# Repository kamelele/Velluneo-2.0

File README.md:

# Velluneo-2.0

[Projekt E27 z wymiennym wkładem LED](hardware/E27/README.md)

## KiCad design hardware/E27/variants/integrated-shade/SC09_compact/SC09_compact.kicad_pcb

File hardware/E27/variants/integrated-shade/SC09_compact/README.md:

Current desk-reviewed laboratory candidate: [SB01-R2](README.SB01-R2.md). Earlier R1 release files and descriptions below are historical.

Historical R1 engineering candidate: [SC09-SB01 simplified procurement](README.SB01.md). The following older text and release-candidate artifacts are historical.

# SC09-ROUTE05 bare-PCB/manual prototype candidate

Current packet: workflow/integrated-shade/compact-09/routing-order-prep/po_poprawkach. PCB51.2x33mm,2layers,1.6mm FR4,1oz,lead-freeHASL; unchangedCAT01 electronics and component placements. The outline adds edge margin, D1 return via is outside its SMD solder land and the bottom AC legend is clear of solder apertures. AC RIGHT/LED LEFT in common topCAD coordinates. Physical vent-face clearance remains5mm. Current exact fabrication release decision remains pending; full-product qualification is not asserted. No order or powered test.

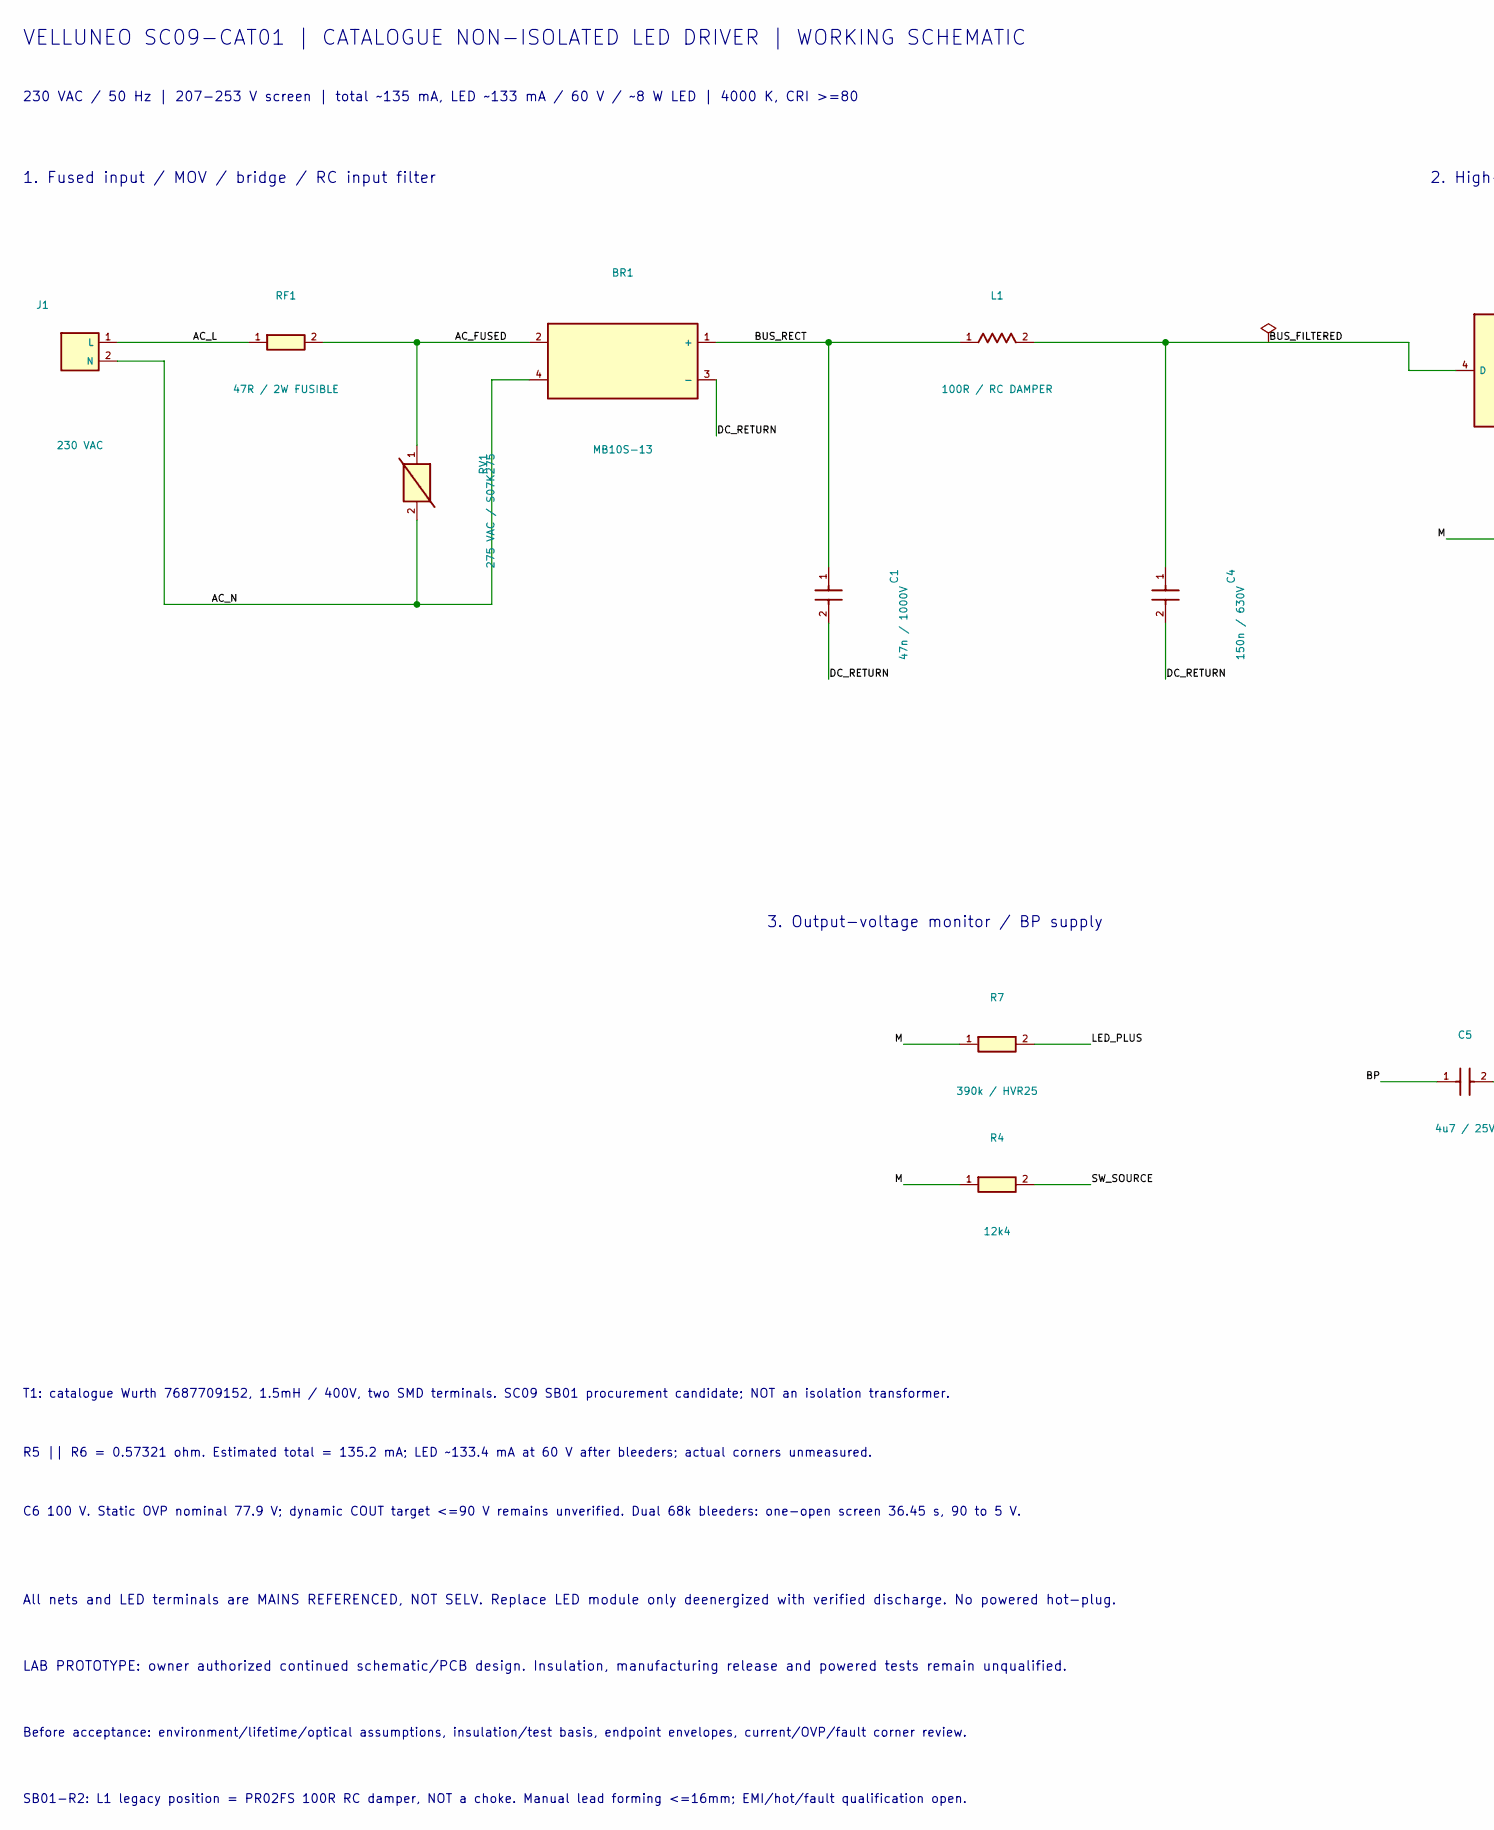
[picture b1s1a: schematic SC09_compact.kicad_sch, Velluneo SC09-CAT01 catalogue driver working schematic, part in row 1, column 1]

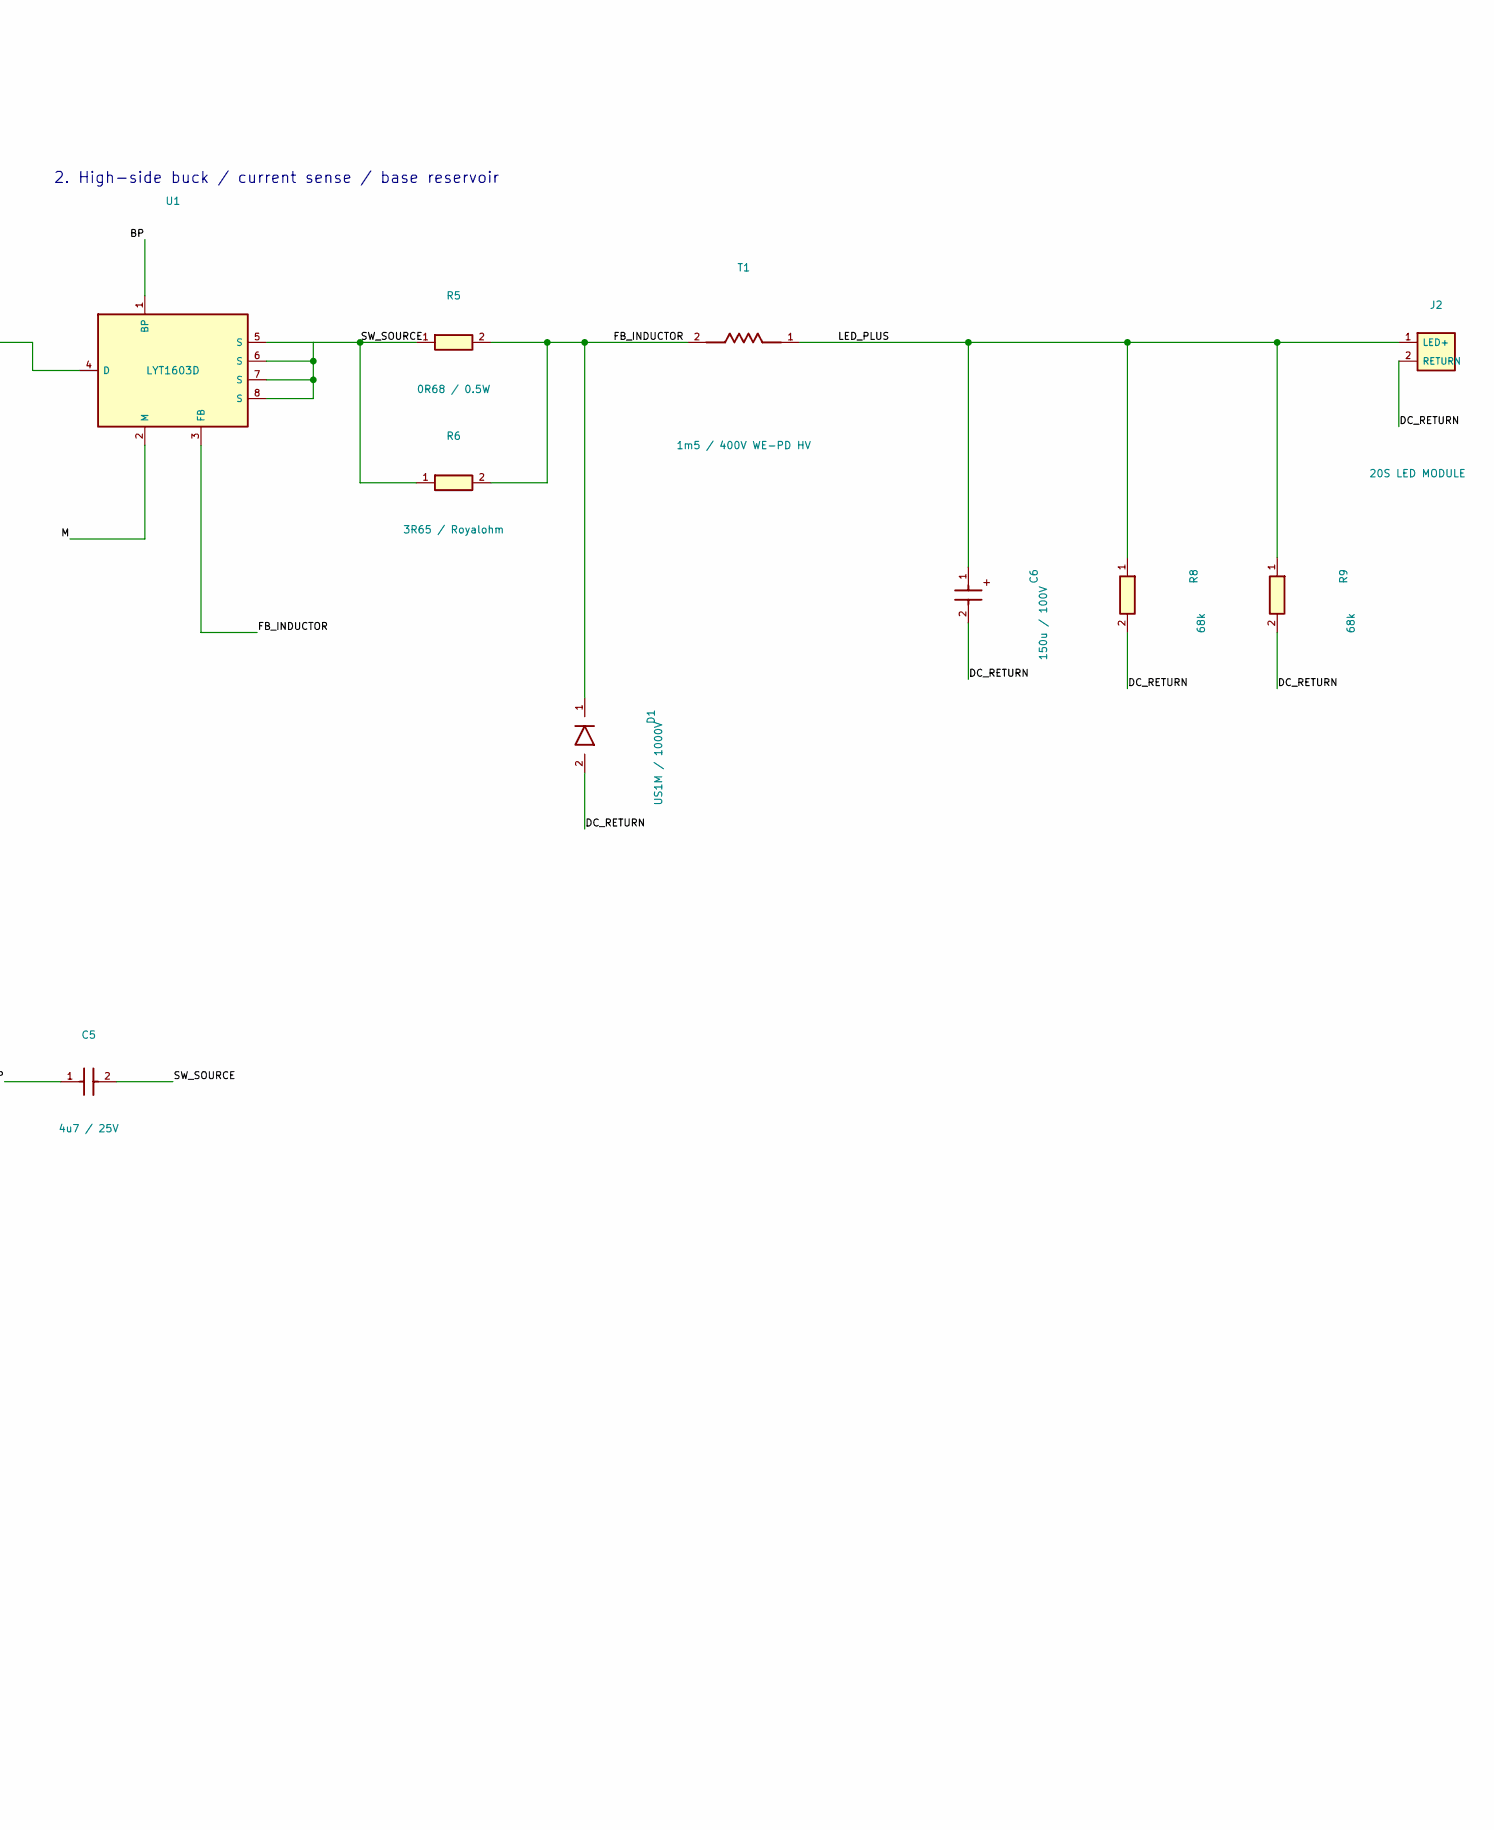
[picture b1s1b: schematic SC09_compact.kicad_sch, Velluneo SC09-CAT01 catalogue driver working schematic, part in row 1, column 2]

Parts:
BR1: MB10S-13; SC09_BR1; MPN MB10S-13
C1: 47n / 1000V; SC09_C1; MPN R76QI24705050J
C4: 150n / 630V; SC09_C4; MPN B32671P6154K000
C5: 4u7 / 25V; SC09_C5; MPN CL21B475KAFNNNE
C6: 150u / 100V; SC09_C6; MPN EEUFS2A151
D1: US1M / 1000V; SC09_D1; MPN US1M-13-F
J1: 230 VAC; SC09_J1; MPN Direct insulated-wire solder pads
J2: 20S LED MODULE; SC09_J2; MPN Direct insulated-wire solder pads
L1: 100R / RC DAMPER; SC09_L1; MPN PR02FS0201000KR500
R4: 12k4; SC09_R4; MPN ERJ-6ENF1242V
R5: 0R68 / 0.5W; SC09_R5; MPN RL1206FR-7W0R68L
R6: 3R65 / Royalohm; SC09_R6; MPN 1206S4F365KT5E
R7: 390k / HVR25; SC09_R7; MPN HVR2500003903FR500
R8: 68k; SC09_R8; MPN RC1206FR-0768KL
R9: 68k; SC09_R9; MPN RC1206FR-0768KL
RF1: 47R / 2W FUSIBLE; SC09_RF1; MPN FW20A47R0JA
RV1: 275 VAC / S07K275; SC09_RV1; MPN B72207S0271K101
T1: 1m5 / 400V WE-PD HV; SC09_T1; MPN 7687709152
U1: LYT1603D; SC09_U1; MPN LYT1603D

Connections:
/AC_FUSED: BR1.2, RF1.2, RV1.1
/AC_L: J1.1 (L), RF1.1
/AC_N: BR1.4, J1.2 (N), RV1.2
/BP: C5.1, U1.1 (BP)
/BUS_FILTERED: C4.1, L1.2, U1.4 (D)
/BUS_RECT: BR1.1 (+), C1.1, L1.1
/DC_RETURN: BR1.3 (-), C1.2, C4.2, C6.2, D1.2 (A), J2.2 (RETURN), R8.2, R9.2
/FB_INDUCTOR: D1.1 (K), R5.2, R6.2, T1.2, U1.3 (FB)
/LED_PLUS: C6.1, J2.1 (LED+), R7.2, R8.1, R9.1, T1.1
/M: R4.1, R7.1, U1.2 (M)
/SW_SOURCE: C5.2, R4.2, R5.1, R6.1, U1.5 (S), U1.6 (S), U1.7 (S), U1.8 (S)

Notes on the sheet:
VELLUNEO SC09-CAT01 | CATALOGUE NON-ISOLATED LED DRIVER | WORKING SCHEMATIC
230 VAC / 50 Hz | 207-253 V screen | total ~135 mA, LED ~133 mA / 60 V / ~8 W LED | 4000 K, CRI >=80
1. Fused input / MOV / bridge / RC input filter
2. High-side buck / current sense / base reservoir
3. Output-voltage monitor / BP supply
T1: catalogue Wurth 7687709152, 1.5mH / 400V, two SMD terminals. SC09 SB01 procurement candidate; NOT an isolation transformer.
R5 || R6 = 0.57321 ohm. Estimated total = 135.2 mA; LED ~133.4 mA at 60 V after bleeders; actual corners unmeasured.
C6 100 V. Static OVP nominal 77.9 V; dynamic COUT target <=90 V remains unverified. Dual 68k bleeders: one-open screen 36.45 s, 90 to 5 V.
All nets and LED terminals are MAINS REFERENCED, NOT SELV. Replace LED module only deenergized with verified discharge. No powered hot-plug.
LAB PROTOTYPE: owner authorized continued schematic/PCB design. Insulation, manufacturing release and powered tests remain unqualified.
Before acceptance: environment/lifetime/optical assumptions, insulation/test basis, endpoint envelopes, current/OVP/fault corner review.
SB01-R2: L1 legacy position = PR02FS 100R RC damper, NOT a choke. Manual lead forming <=16mm; EMI/hot/fault qualification open.

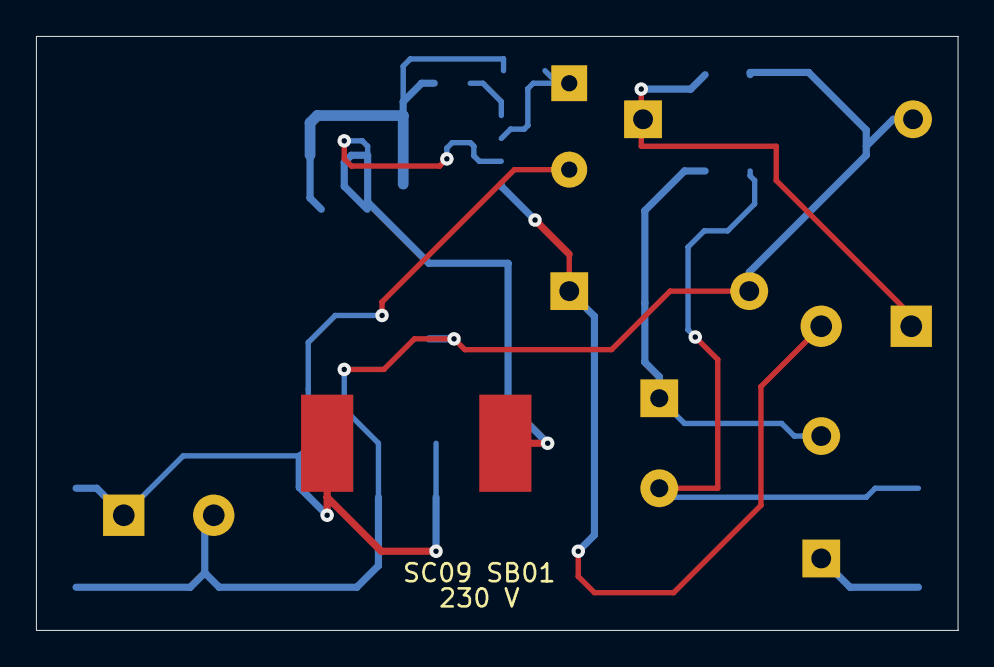
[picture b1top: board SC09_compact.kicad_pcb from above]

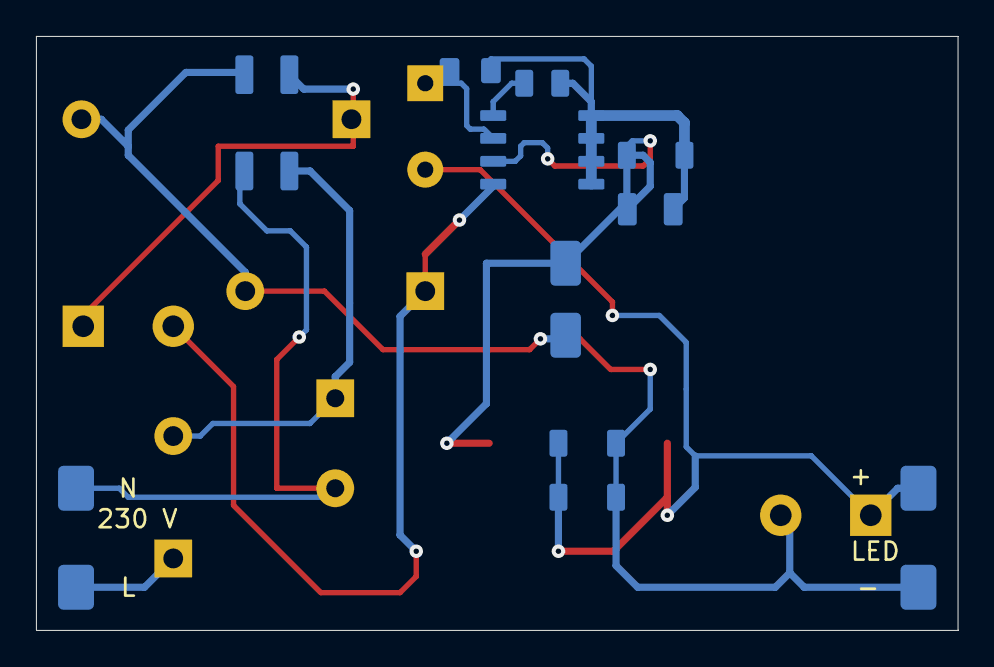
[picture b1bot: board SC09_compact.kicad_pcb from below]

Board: 2 copper layers, 51.2 x 33.0 mm, 19 parts (11 on the bottom side), 11 nets.

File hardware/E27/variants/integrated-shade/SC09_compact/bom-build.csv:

Reference,Value,MPN,Package,Source
J1,230V AC input,Direct insulated-wire solder pads,2wirepads,Actual owner board-only interface
RF1,47ohm 5% 2W fusible,FW20A47R0JA,"axial, same FW20A12x6mm",https://www.bourns.com/docs/Product-Datasheets/FW.pdf
RV1,275VAC MOV 21J,B72207S0271K101,TDK S07 standard radial P5,https://www.tme.eu/Document/94891b49d586e9338877713baac923fe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
BR1,1000V 0.8A bridge,MB10S-13,MBS/SO4,https://www.diodes.com/datasheet/download/MB10S.pdf
C1,47nF 5% 1000V pulse film,R76QI24705050J,KEMET R76 radial P15,https://www.tme.eu/Document/e17ad82984cff1e1d067933eb1fdd0b8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
L1,100ohm 10% 2W RC damper (legacy L1 position),PR02FS0201000KR500,"axial PR02-FS, vertical manual forming on existing 5.0038mm TH pair",https://www.vishay.com/docs/28915/pr02fs.pdf
C4,150nF 630V 10%,B32671P6154K000,radial P10,https://product.tdk.com/en/search/capacitor/film/snubbering_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
U1,LYTSwitch-1,LYT1603D,SO8,https://www.power.com/sites/default/files/documents/lytswitc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
C5,4.7uF 25V X7R,CL21B475KAFNNNE,0805,https://product.samsungsem.com/mlcc/CL21B475KAFNNN.do
R4,12.4kohm 1%,ERJ-6ENF1242V,0805,https://industrial.panasonic.com/ww/products/pt/general-purp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
R5,0.68ohm 1% 0.5W,RL1206FR-7W0R68L,1206,https://www.power.com/sites/default/files/documents/rdr464.pdf
R6,3.65ohm 1% 0.25W,1206S4F365KT5E,1206,https://www.tme.eu/pl/details/smd1206-3.65r-1%25/rezystory-s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
D1,1000V 1A ultrafast,US1M-13-F,SMA,https://www.diodes.com/datasheet/download/US1M.pdf
T1,1.5mH 20% 400V,7687709152,"WE-PD HV 1280 SMD,12.5x12.5x10.5max",https://www.we-online.com/components/products/datasheet/7687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
C6,150uF 100V 20%,EEUFS2A151,radial P5 mounted horizontal,https://industrial.panasonic.com/sa/products/pt/aluminum-cap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
R7,390kohm 1% 1.6kV,HVR2500003903FR500,axial,https://www.vishay.com/docs/30260/hvr2537.pdf
R8,68kohm 1% 0.25W,RC1206FR-0768KL,1206,https://www.yageogroup.com/component-documentation/download/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
R9,68kohm 1% 0.25W,RC1206FR-0768KL,1206,https://www.yageogroup.com/component-documentation/download/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
J2,LED module output,Direct insulated-wire solder pads,2wirepads,Actual owner integratedLED+shade module

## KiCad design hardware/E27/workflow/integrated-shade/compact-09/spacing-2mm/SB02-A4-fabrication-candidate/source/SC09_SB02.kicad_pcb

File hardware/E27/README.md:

# Velluneo E27

Żarówka E27 230 V z wymiennym wkładem Ø30 mm. Trzy wersje barwy (2700 K, 4000 K i 6500 K) korzystają z tego samego interfejsu i mechanizmu.

- **Zasilacz dzielony · wariant prototypowy** · [moc Rev K 55,5 × 34 mm](outputs/Zasilacz_RevK_Moc/README.md) · [sterowanie Rev H 30 × 25 mm](outputs/Zasilacz_RevH_Sterowanie/README.md) · [wspólny podgląd](outputs/Zasilacz_RevK_Moc/Podglady/Zasilacz_RevK_RevH_razem.png) · [pakiet JLCPCB](Pakiet_prototypu_JLCPCB.md)
- **Zasilacz dzielony · wariant archiwalny do oceny** · [moc Rev H 55,5 × 34 mm](outputs/Zasilacz_RevH_Moc/README.md) · [sterowanie Rev G 30 × 25 mm](outputs/Zasilacz_RevG_Sterowanie/README.md)
- [Studium Rev L · kompletne trasowanie valley-fill na czterech warstwach](outputs/Studium_RevL_ValleyFill/README.md)
- [Studium Rev J · korekcja harmonicznych i rozmieszczenie valley-fill](outputs/Studium_RevJ_ValleyFill/README.md)
- **Zasilacz dzielony Rev G** · [moc Rev G 55,5 × 34 mm](outputs/Zasilacz_RevG_Moc/README.md) · [sterowanie Rev G 30 × 25 mm](outputs/Zasilacz_RevG_Sterowanie/README.md) · [wspólny podgląd](outputs/Zasilacz_RevG_Moc/Podglady/Zasilacz_RevG_razem.png)
- **Zasilacz dzielony Rev F** · [płytka mocy 55,5 × 34 mm](outputs/Zasilacz_RevF_Moc/README.md) · [sterowanie 30 × 25 mm](outputs/Zasilacz_RevF_Sterowanie/README.md) · pliki do wyceny technologicznej JLCPCB
- [Zasilacz Rev E · mniejsza płytka, wariant dzielony i podglądy 3D](outputs/Studium_RevE/README.md)
- [Zasilacz Rev D · jedna płytka do wyceny w JLCPCB](outputs/Zasilacz_RevD_JLCPCB/README.md)
- [Zasilacz Rev B1 · odprowadzanie ciepła przez PCB](outputs/Zasilacz_RevB1/README.md) · [weryfikacja KiCad](outputs/Zasilacz_RevB1/Weryfikacja_KiCad_RevB1.md)
- [Zasilacz Rev B2 · moduł prób ochrony zwarciowej](outputs/Zasilacz_RevB2_Ochrona/README.md) · [wyniki modelu](outputs/Zasilacz_RevB2_Ochrona/Model_RevB2_przypadki.csv)
- [Rewizja B zasilacza i wyniki weryfikacji](outputs/Raport_E27_RevB.md) · [projekt KiCad](outputs/Zasilacz_RevB) · [BOM](outputs/BOM_Zasilacz_RevB.csv)
- [Projekt wkładu LED](outputs/Wklad_LED) · [mechanizm wymiany](outputs/Mechanizm_E27_RevA.svg)
- [Pakiet KiCad Rev B](outputs/E27_RevB_pakiet_KiCad.zip) · [plan prób](outputs/Plan_prob_RevB.md)
- [Dokumentacja rewizji A](outputs/Raport_E27_RevA.md) · [pakiet Rev A](outputs/E27_RevA_pakiet_KiCad.zip)
- [Studium Rev C](outputs/Studium_RevC/README.md) · [model mechaniczny KiCad](outputs/Studium_RevC/E27_RevC_Gabaryty.kicad_pcb) · [specyfikacja próbek transformatora EFD20](outputs/Studium_RevC/RFQ_T1_EFD20.md)

Rewizje zasilacza są dokumentacją rozwojową. Audyt wykazał błąd składni reguł odstępu w historycznych projektach mocy. Ich wyniki DRC mają wartość archiwalną. Pakiet mocy Rev H wstrzymano do zamówienia. [Wyniki ponownej kontroli](outputs/Zasilacz_RevH_Moc/Weryfikacja_RevH.md). Pliki oznaczone `Produkcja_DO_PRZEGLADU` służą do przeglądu technologicznego. Przed próbami z siecią konieczny jest przegląd transformatora, ochrony, izolacji kompletnego zespołu oraz stanowiska.

Skrypty w katalogu [work](work) uruchamia się z katalogu `hardware/E27` z KiCad 10.0.8. Regeneracja zmienia pliki w `outputs`. Na Windows skrypty zakładają standardową ścieżkę instalacji KiCad.

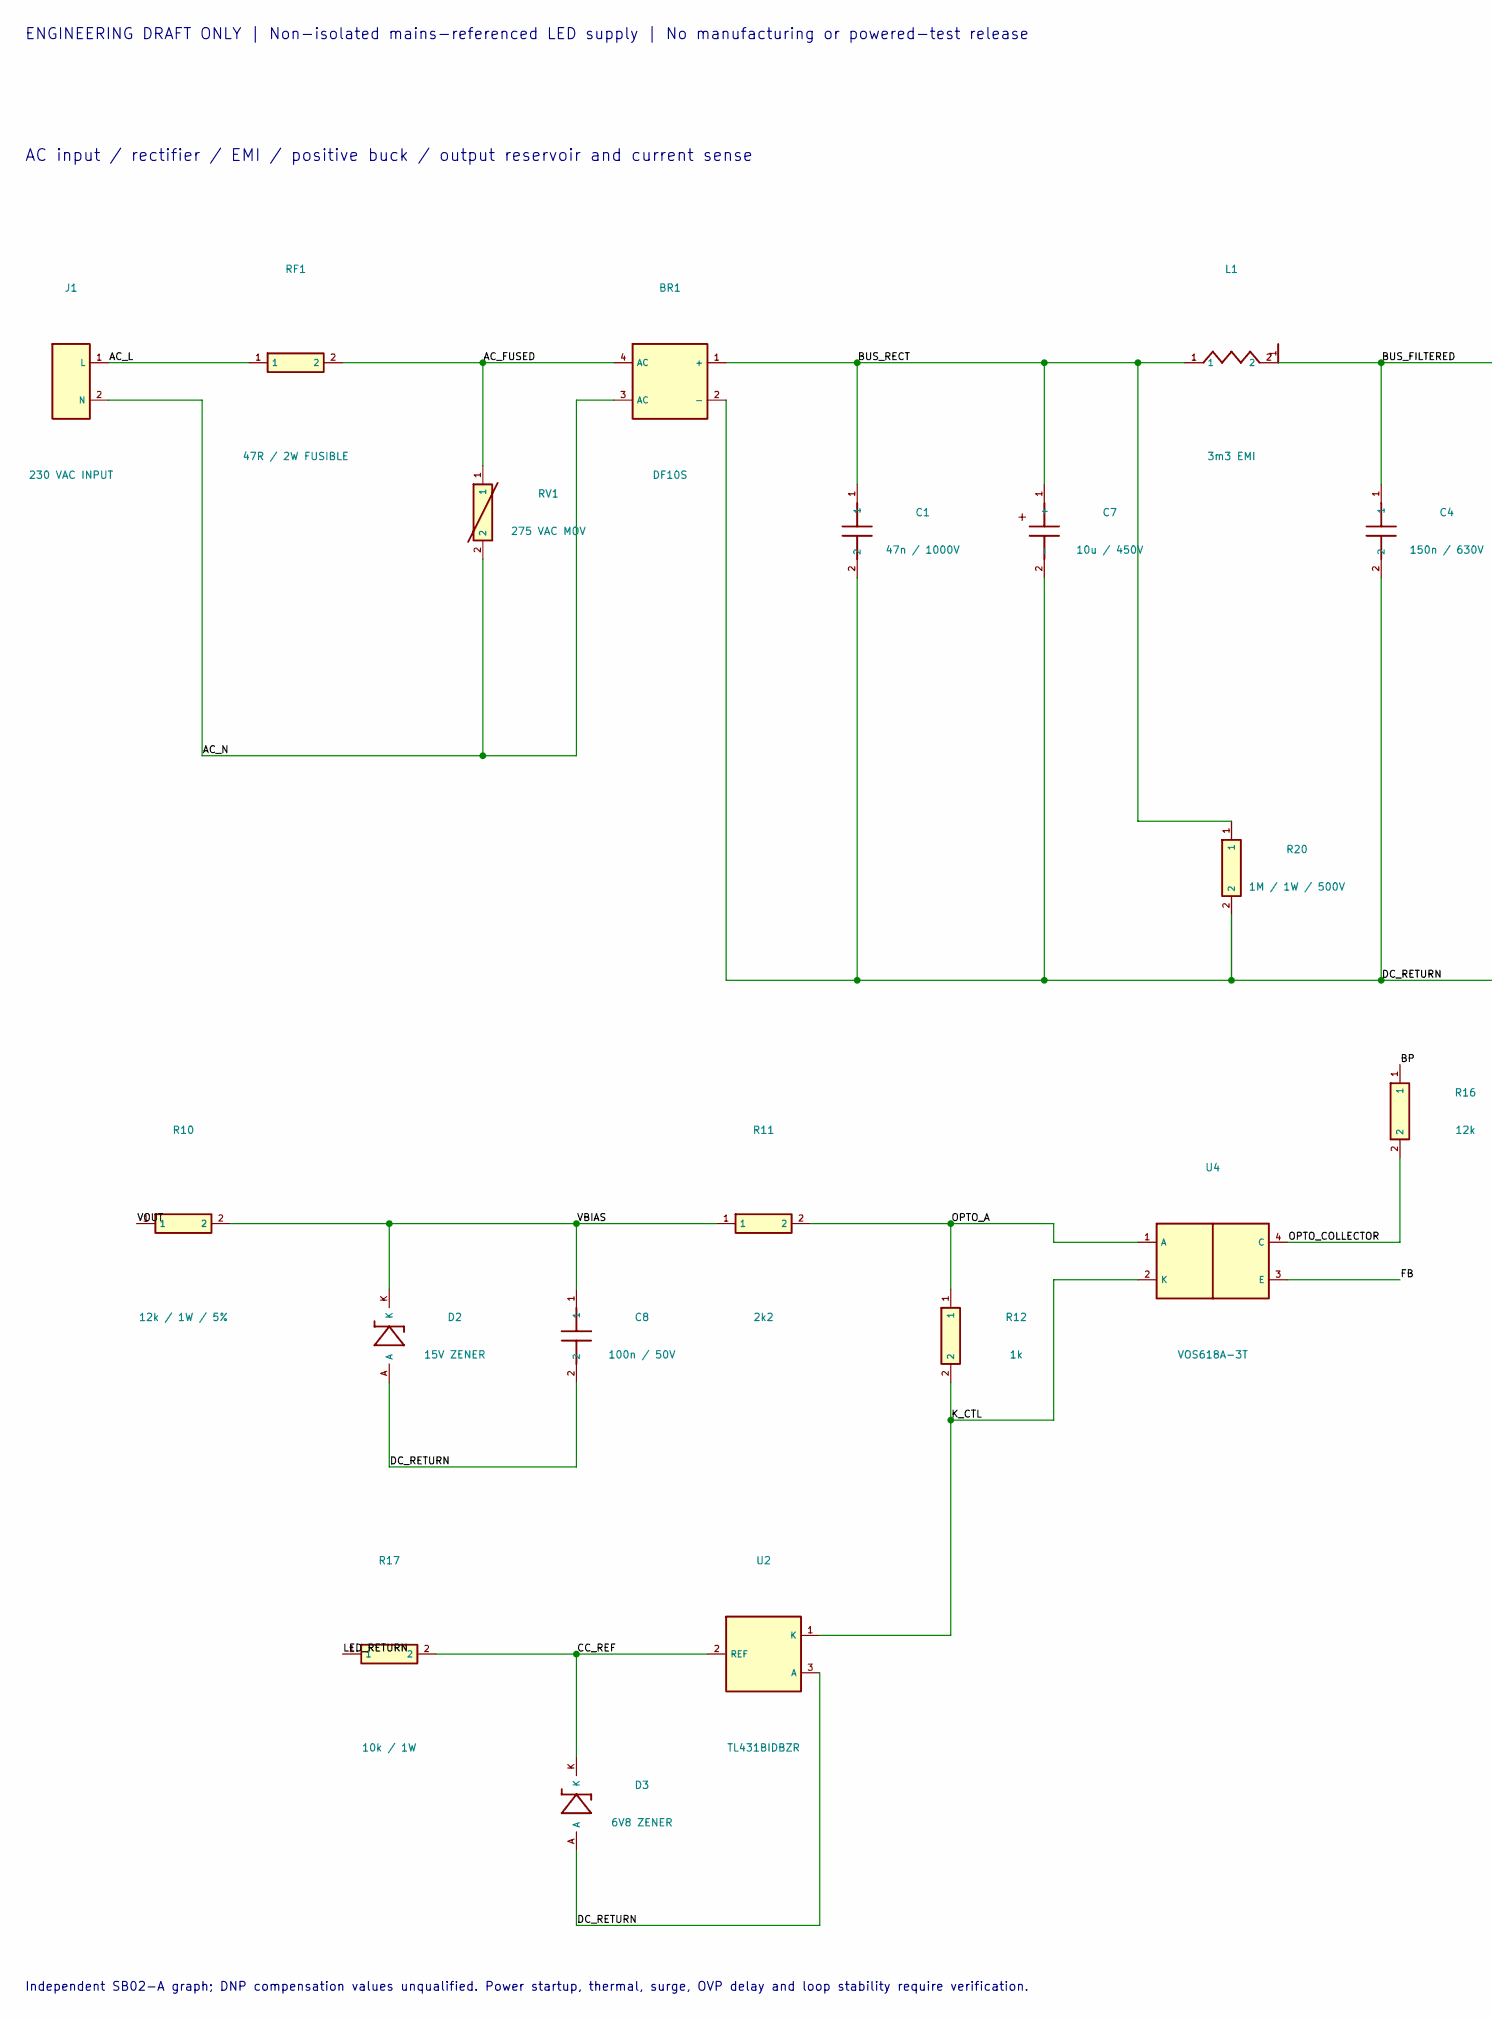
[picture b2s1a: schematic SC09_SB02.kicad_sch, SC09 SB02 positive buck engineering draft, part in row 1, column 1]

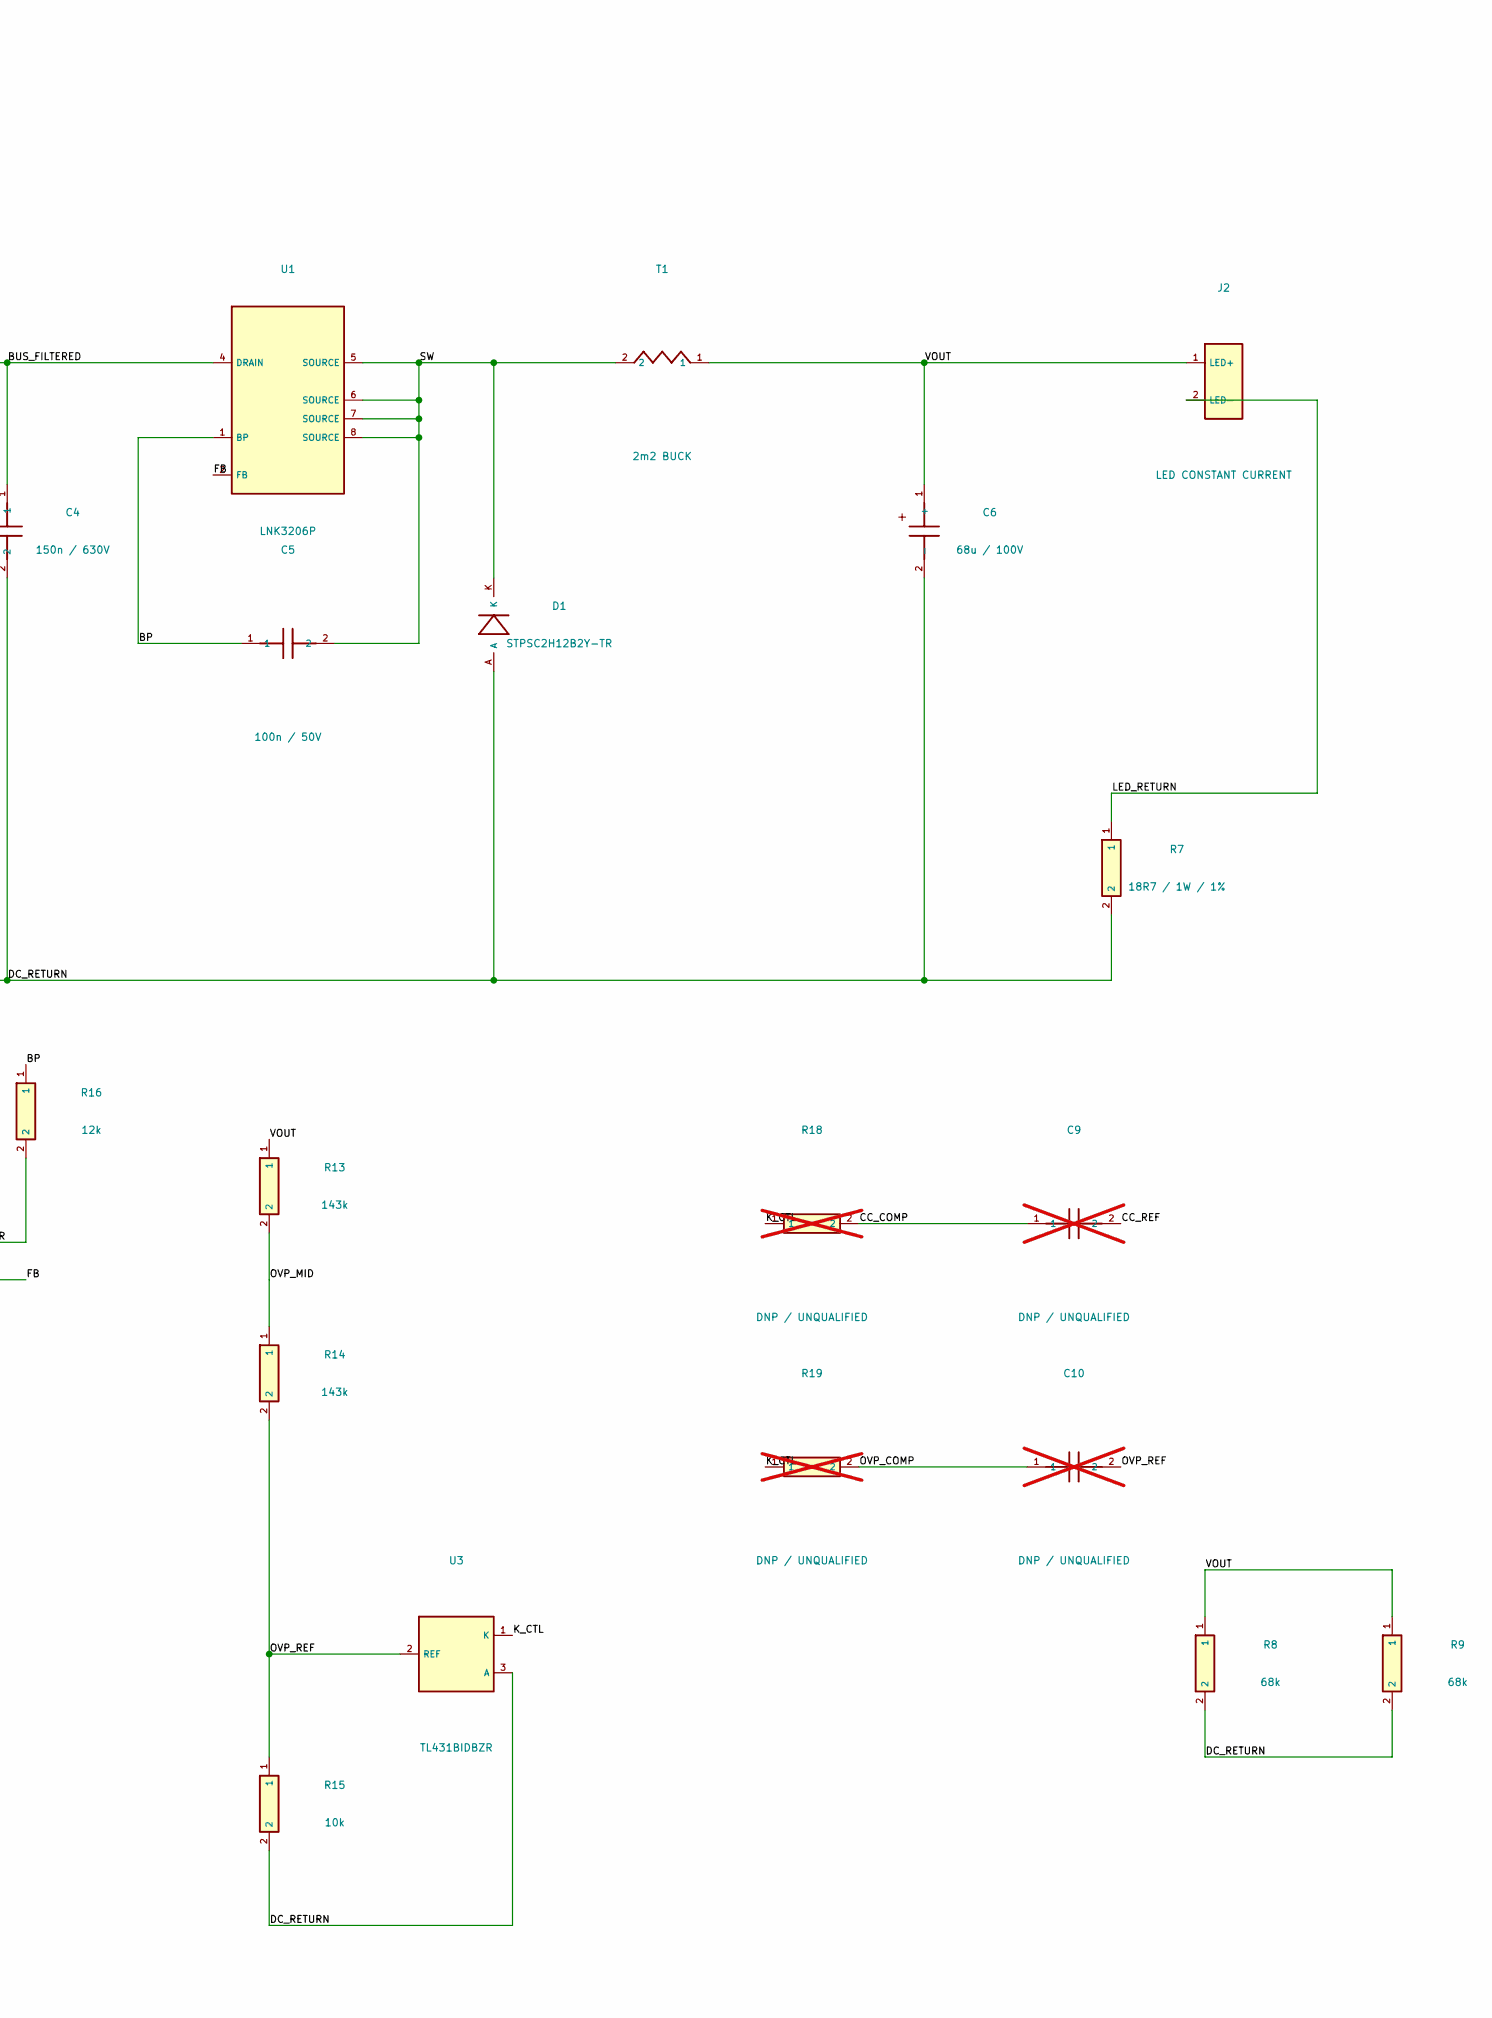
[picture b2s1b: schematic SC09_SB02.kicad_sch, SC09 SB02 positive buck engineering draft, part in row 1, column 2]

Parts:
BR1: DF10S; SB02_BR1; MPN DF10S
C1: 47n / 1000V; SB02_C1; MPN R76QI24705050J
C4: 150n / 630V; SB02_C4; MPN B32671P6154K000
C5: 100n / 50V; SB02_C5; MPN CL21B104KBCNNNC
C6: 68u / 100V; SB02_C6; MPN EEU-FS2A680
C7: 10u / 450V; SB02_C7; MPN 450BXW10MEFR10X16
C8: 100n / 50V; SB02_C8; MPN CL21B104KBCNNNC
C9: DNP / UNQUALIFIED; SB02_C9; MPN DNP; optional compensation position, va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; not fitted
C10: DNP / UNQUALIFIED; SB02_C10; MPN DNP; optional compensation position, va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; not fitted
D1: STPSC2H12B2Y-TR; SB02_D1; MPN STPSC2H12B2Y-TR
D2: 15V ZENER; SB02_D2; MPN BZX55C15-TAP
D3: 6V8 ZENER; SB02_D3; MPN BZX55C6V8-TAP
J1: 230 VAC INPUT; SB02_J1; MPN Wire solder connection; no supplied con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
J2: LED CONSTANT CURRENT; SB02_J2; MPN Wire solder connection; no supplied con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
L1: 3m3 EMI; SB02_L1; MPN 768772332
R7: 18R7 / 1W / 1%; SB02_R7; MPN CRCW251218R7FKEG
R8: 68k; SB02_R8; MPN RC2512FK-0768KL
R9: 68k; SB02_R9; MPN RC2512FK-0768KL
R10: 12k / 1W / 5%; SB02_R10; MPN MOR01SJ0123A10
R11: 2k2; SB02_R11; MPN RC0805FR-072K2L
R12: 1k; SB02_R12; MPN RC0805FR-071KL
R13: 143k; SB02_R13; MPN ERJ-1TNF1433U
R14: 143k; SB02_R14; MPN ERJ-1TNF1433U
R15: 10k; SB02_R15; MPN RC0805FR-0710KL
R16: 12k; SB02_R16; MPN RC0805FR-0712KL
R17: 10k / 1W; SB02_R17; MPN CRCW251210K0FKTG
R18: DNP / UNQUALIFIED; SB02_R18; MPN DNP; optional compensation position, va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; not fitted
R19: DNP / UNQUALIFIED; SB02_R19; MPN DNP; optional compensation position, va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; not fitted
R20: 1M / 1W / 500V; SB02_R20; MPN CRCW25121M00FKEG
RF1: 47R / 2W FUSIBLE; SB02_RF1; MPN FW20A47R0JA
RV1: 275 VAC MOV; SB02_RV1; MPN B72207S0271K101
T1: 2m2 BUCK; SB02_T1; MPN 7687709222
U1: LNK3206P; SB02_U1; MPN LNK3206P
U2: TL431BIDBZR; SB02_U2; MPN TL431BIDBZR
U3: TL431BIDBZR; SB02_U3; MPN TL431BIDBZR
U4: VOS618A-3T; SB02_U4; MPN VOS618A-3T

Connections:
/AC_FUSED: BR1.4 (AC), RF1.2, RV1.1
/AC_L: J1.1 (L), RF1.1
/AC_N: BR1.3 (AC), J1.2 (N), RV1.2
/BP: C5.1, R16.1, U1.1 (BP)
/BUS_FILTERED: C4.1, L1.2, U1.4 (DRAIN)
/BUS_RECT: BR1.1 (+), C1.1, C7.1 (+), L1.1, R20.1
/CC_COMP: C9.1, R18.2
/CC_REF: C9.2, D3.K, R17.2, U2.2 (REF)
/DC_RETURN: BR1.2 (-), C1.2, C4.2, C6.2 (-), C7.2 (-), C8.2, D1.A, D2.A, D3.A, R7.2, R8.2, R9.2, R15.2, R20.2, U2.3 (A), U3.3 (A)
/FB: U1.2 (FB), U4.3 (E)
/K_CTL: R12.2, R18.1, R19.1, U2.1 (K), U3.1 (K), U4.2 (K)
/LED_RETURN: J2.2 (LED-), R7.1, R17.1
/OPTO_A: R11.2, R12.1, U4.1 (A)
/OPTO_COLLECTOR: R16.2, U4.4 (C)
/OVP_COMP: C10.1, R19.2
/OVP_MID: R13.2, R14.1
/OVP_REF: C10.2, R14.2, R15.1, U3.2 (REF)
/SW: C5.2, D1.K, T1.2, U1.5 (SOURCE), U1.6 (SOURCE), U1.7 (SOURCE), U1.8 (SOURCE)
/VBIAS: C8.1, D2.K, R10.2, R11.1
/VOUT: C6.1 (+), J2.1 (LED+), R8.1, R9.1, R10.1, R13.1, T1.1

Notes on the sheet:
AC input / rectifier / EMI / positive buck / output reservoir and current sense
ENGINEERING DRAFT ONLY | Non-isolated mains-referenced LED supply | No manufacturing or powered-test release
Independent SB02-A graph; DNP compensation values unqualified. Power startup, thermal, surge, OVP delay and loop stability require verification.

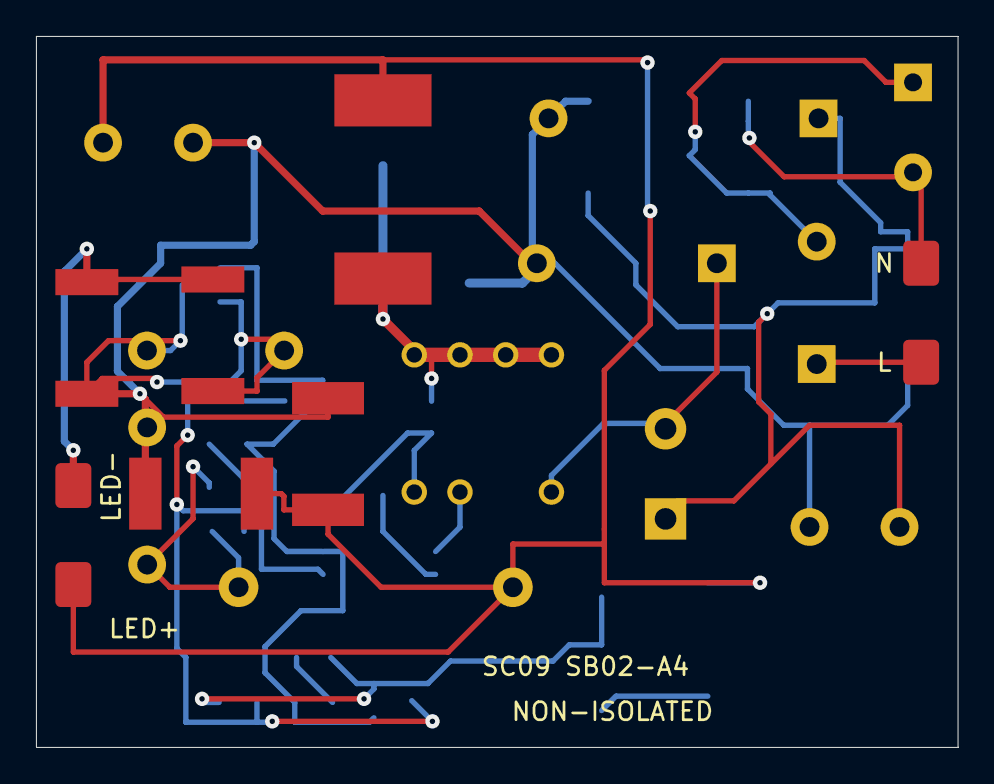
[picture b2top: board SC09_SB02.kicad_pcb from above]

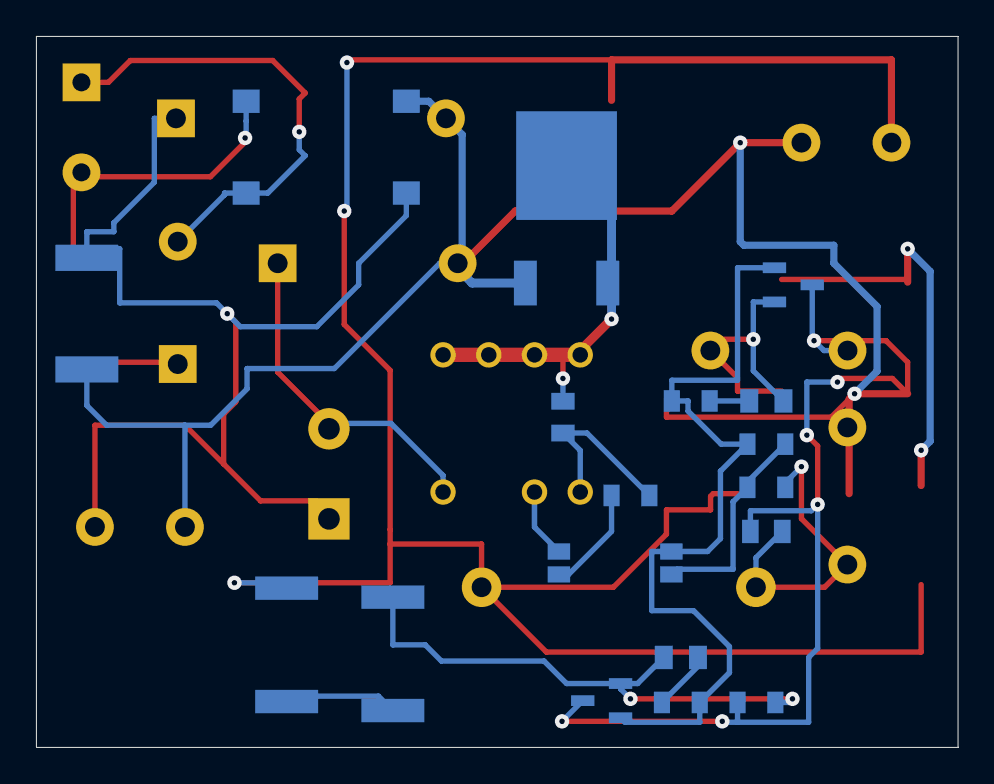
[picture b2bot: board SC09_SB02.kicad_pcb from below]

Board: 2 copper layers, 51.2 x 39.5 mm, 36 parts (20 on the bottom side), 20 nets.
